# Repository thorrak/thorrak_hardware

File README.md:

# Thorrak's Hardware Designs
This repo is a collection of PCBs and other hardware designs I've made for various projects I've released. More information can be found on pages for each of the projects themselves.

**Note** - While the majority of the hardware for my projects is contained in this repo, the software is broken out into individual projects on GitHub. Most firmware can be flashed using [BrewFlasher](http://www.brewflasher.com/).

## BrewPi-ESP

The BrewPi-ESP project reimplements the BrewPi firmware on an ESP8266, ESP32, and ESP32-S2. 

- [Hardware Designs](BrewPi-ESP.md)
- [Project on GitHub](https://github.com/thorrak/brewpi-esp8266)

## TiltBridge

The TiltBridge project provides a Bluetooth-to-WiFi bridge for Tilt Hydrometers

- [Hardware/Container Designs](TiltBridge.md)
- [Project on GitHub](https://github.com/thorrak/tiltbridge/)

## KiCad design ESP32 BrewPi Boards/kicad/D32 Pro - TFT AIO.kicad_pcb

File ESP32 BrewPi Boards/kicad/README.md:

ESP32 BrewPi Controller Boards
==============================

# NOTE - This document is NOT complete/verified yet. 
## Please do not base a build on this doc without consulting Thorrak directly first!

Although the "heart" of a BrewPi controller is the microprocessor running the BrewPi-compatible firmware, without other connected components that microcontroller cannot sense temperature, control power, or do any of the other things that make a temperature controller useful. For the ESP32 version of this project, I have designed a single, "all-in-one" PCB that should work for virtually all builds. 

| Board Design                                              | Tindie Order Link                               | OSHPark Order Link                                     |
|-----------------------------------------------------------|-------------------------------------------------|--------------------------------------------------------|
| [All-in-One D32 / D32 Pro](D32%20Pro%20-%20-TFT%20AIO.md) | [Order](https://www.tindie.com/products/27251/) | [Order](https://oshpark.com/)  |

This board supports the following features:
- Supports both [LoLin D32](https://www.wemos.cc/en/latest/d32/d32.html) and [LoLin D32 Pro](https://www.wemos.cc/en/latest/d32/d32_pro.html) controllers
- Supports both IIC and TFT screens
- Supports both the specific [LoLin D32 Pro screen](https://www.aliexpress.com/item/2251832733414978.html), as well as generic TFT screens
- Supports emulating a NTC10k temperature sensor, allowing control of certain glycol chillers (IceMaster Max2/Max4 and possibly others)
- Selectable OneWire voltage
- Optional TH-only configuration for easy assembly

### About Parts Links, Order Links, & Vendors

The BOM links provided are intended to serve as examples of the parts needed and are not the only place to source the  parts listed.  Generally speaking, AliExpress is less expensive for parts.  The trade-off is that sometimes you are  buying 100 at a time, and in most cases you are waiting for shipping.  DigiKey, Mouser, or other project part suppliers  will probably have these parts as well and can generally ship much faster (albeit at much higher cost).

For convenience, order links are provided on each of the PCB's pages. Bare PCBs can be ordered from OshPark using the link provided, or from your PCB-vendor-of-choice by uploading the Gerber files (found in the `production` folder). I also sometimes have PCBs available for sale on Tindie - including in some cases, either fully- or partially-assembled boards. When you purchase through Tindie you are receiving a board or parts directly from me. 

#### TH Parts required to assemble the PCB

| Part                                                                                                                                       | Qty |
|--------------------------------------------------------------------------------------------------------------------------------------------|-----|
| [PCB](https://www.tindie.com/products/27251/)                                                                                              | 1   |
| [RJ45 Modular Jack w/no shield](https://www.digikey.com/en/products/detail/stewart-connector/SS-90000-001/14548964)                        | 1   |
| [2-terminal Screw Clamp](https://www.digikey.com/en/products/detail/w%C3%BCrth-elektronik/691137710002/6644051)                            | 1   |
| [4-Pin Male Pin Header](https://www.digikey.com/en/products/detail/sullins-connector-solutions/PRPC040SAAN-RC/2775214)                     | 2   |
| [3-Pin Male Pin Header](https://www.digikey.com/en/products/detail/sullins-connector-solutions/PRPC040SAAN-RC/2775214)                     | 1   |
| [2-Pin Male Pin Header](https://www.digikey.com/en/products/detail/sullins-connector-solutions/PRPC040SAAN-RC/2775214)                     | 1   |
| [16-Pin Female Pin Header](https://www.digikey.com/en/products/detail/sullins-connector-solutions/PPTC161LFBN-RC/810154)                   | 2   |
| [10-Pin (2x5) Box Header](https://www.digikey.com/en/products/detail/amphenol-cs-commercial-products/G821EU210AGM00Y/13683147) (Optional*) | 1   |
| [2.54mm Jumper](https://www.digikey.com/en/products/detail/sullins-connector-solutions/STC02SYAN/76372)**                                  | 1   |

*- The 10-pin box header is optional, but enables the use of a non-Lolin TFT screen attached to an LCD breakout PCB. If using an IIC screen or the [LoLin D32 Pro screen](https://www.aliexpress.com/item/2251832733414978.html) + [cable](https://www.aliexpress.com/item/2251832662518722.html), this can be left off.
**- The 2.54mm jumper is probably included on the 2-channel relay board you will purchase as part of the "common component" set below

### SMD Components required to assemble the PCB

Note - You will not need the following if you purchased the partially-assembled PCB from my [Tindie store](https://www.tindie.com/products/27251/). 

This board supports assembly with both SMD and TH components -- you can choose between the SMD components linked below and the TH components in the second table. You will not need both. The SMD components will enable the LCD2004 screen option - this screen will not work if you use the TH component set. 

| SMD Parts                                                                                                                     | Qty |
|-------------------------------------------------------------------------------------------------------------------------------|-----|
| [10k 0805 Resistor](https://www.digikey.com/en/products/detail/stackpole-electronics-inc/RNCP0805FTD10K0/2240262)             | 4   |
| [4.7k 0805 Resistor](https://www.digikey.com/en/products/detail/te-connectivity-passive-product/CRGCQ0805J4K7/8576740)        | 1   |
| [0.1uF (100nF) 0805 Capacitor](https://www.digikey.com/en/products/detail/samsung-electro-mechanics/CL21B104KACNNNC/3886757)  | 2   |
| [1.0uF 0805 Capacitor](https://www.digikey.com/en/products/detail/samsung-electro-mechanics/CL21B105KAFNNNE/3886724)          | 2   |
| [BSS138 MOSFET](https://www.digikey.com/en/products/detail/onsemi/BSS138/244210)                                              | 2   |
| [EL817S1(TU)-G Optocoupler](https://www.digikey.com/en/products/detail/everlight-electronics-co-ltd/EL8171S1-TU-G/9446028)    | 1   |
| [100R 0805 Resistor](https://www.digikey.com/en/products/detail/yageo/RC0805FR-07100RL/727543)                                | 1   |
| [8.2k 0805 Resistor](https://www.digikey.com/en/products/detail/stackpole-electronics-inc/RMCF0805JT8K20/1757870)             | 1   |
| [27k 0805 Resistor](https://www.digikey.com/en/products/detail/stackpole-electronics-inc/RMCF0805JT27K0/1757886)              | 1   |

This is the optional, alternative TH part set. You **DO NOT** need these parts if you ordered either the SMD parts above, or the partially-assembled PCB:

| Alternative TH Part                                                                                      | Qty |
|----------------------------------------------------------------------------------------------------------|-----|
| [4.7k Resistor](https://www.digikey.com/en/products/detail/stackpole-electronics-inc/CF14JT4K70/1741428) | 1   |
| [0.1uF (100nF) Capacitor](https://www.digikey.com/en/products/detail/kemet/C315C104M5U5TA/817927)        | 2   |
| [1.0uF Capacitor](https://www.digikey.com/en/products/detail/kemet/C320C105K5N5TA7301/12701373)          | 2   |

## Other Required Components

Below are the other "required" components for almost every build: 

| Component                                                                            | Qty |
|--------------------------------------------------------------------------------------|-----|
| [LOLIN D32 Pro](https://www.aliexpress.com/item/2251832696801305.html)               | 1   |
| [2-Channel 5V Relay Board](https://www.aliexpress.com/item/32997387727.html)         | 1   |
| [Ethernet cable](https://www.aliexpress.com/item/32694241950.html)                   | 1   |
| [5V 2A Power Supply Module](https://www.aliexpress.com/item/32900418425.html)        | 1   |
| [Dupont Cables (Female-to-Female)](https://www.aliexpress.com/item/33039596089.html) | 13* |

In addition to the above, this PCB is intended to be used in conjunction with a separate "Sensor Breakout Board" which is then connected to this PCB via the RJ-45 (ethernet) cable listed above. To complete a full controller, you will need the components listed on the [Sensor Board](../../BrewPi%20Sensor%20Boards/README.md) pages as well.

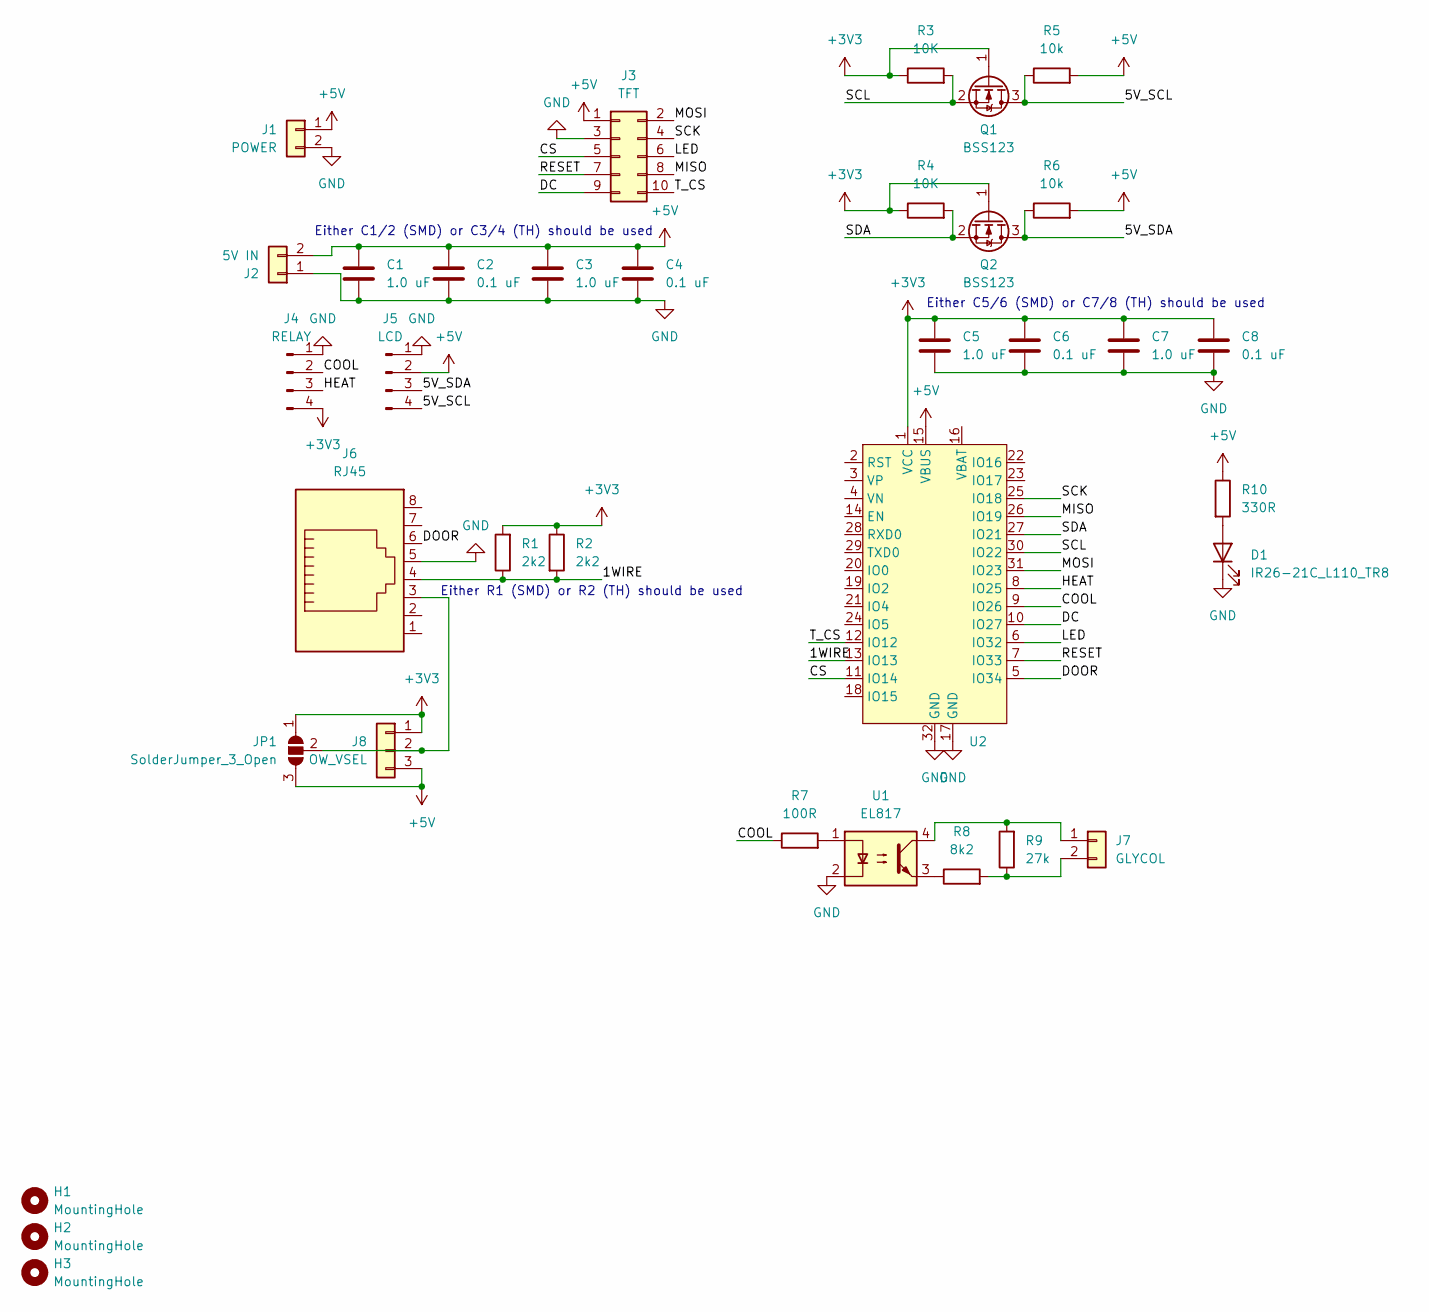
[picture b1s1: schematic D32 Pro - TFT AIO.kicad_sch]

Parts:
C1, C5: 1.0 uF; C_0805_2012Metric_Pad1.18x1.45mm_HandSolder; LCSC C28323
C2, C6: 0.1 uF; C_0805_2012Metric_Pad1.18x1.45mm_HandSolder; LCSC C49678
C3, C7: 1.0 uF; C_Disc_D3.0mm_W1.6mm_P2.50mm
C4, C8: 0.1 uF; C_Disc_D3.0mm_W1.6mm_P2.50mm
D1: IR26-21C_L110_TR8; LED_0805_2012Metric_Pad1.15x1.40mm_HandSolder; LCSC C2297
H1, H2, H3: MountingHole; MountingHole_3.2mm_M3
J1: POWER; PhoenixContact_MSTBVA_2,5_2-G-5,08_1x02_P5.08mm_Vertical
J2: 5V IN; PinHeader_1x02_P2.54mm_Vertical
J3: TFT; IDC-Header_2x05_P2.54mm_Vertical; LCSC C5665
J4: RELAY; PinHeader_1x04_P2.54mm_Vertical
J5: LCD; PinHeader_1x04_P2.54mm_Vertical
J6: RJ45; RJ45_Amphenol_54602-x08_Horizontal; LCSC C3000202
J7: GLYCOL; PinHeader_1x02_P2.54mm_Vertical
J8: OW_VSEL; PinHeader_1x03_P2.54mm_Vertical
JP1: SolderJumper_3_Open; SolderJumper-3_P1.3mm_Open_RoundedPad1.0x1.5mm
Q1, Q2: BSS123; SOT-23-3; LCSC C7420338
R1: 2k2; R_0805_2012Metric_Pad1.15x1.40mm_HandSolder; LCSC C17520
R2: 2k2; R_Axial_DIN0204_L3.6mm_D1.6mm_P1.90mm_Vertical
R3, R4: 10K; R_0805_2012Metric_Pad1.15x1.40mm_HandSolder; LCSC C17414
R5, R6: 10k; R_0805_2012Metric_Pad1.15x1.40mm_HandSolder; LCSC C17414
R7: 100R; R_0805_2012Metric_Pad1.15x1.40mm_HandSolder; LCSC C17408
R8: 8k2; R_0805_2012Metric_Pad1.15x1.40mm_HandSolder; LCSC C17828
R9: 27k; R_0805_2012Metric_Pad1.15x1.40mm_HandSolder; LCSC C17593
R10: 330R; R_0805_2012Metric_Pad1.20x1.40mm_HandSolder; LCSC C17630
U1: EL817; DIP-4_W8.89mm_SMDSocket_LongPads; LCSC C106900
U2: Lolin_D32

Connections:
+3V3: C5.1, C6.1, C7.1, C8.1, J4.4, J8.1, JP1.1 (A), Q1.1 (G), Q2.1 (G), R1.2, R2.1, R3.1, R4.1, U2.1 (VCC)
+5V: C1.1, C2.1, C3.1, C4.1, J1.1, J2.2, J3.1, J5.2, J8.3, JP1.3 (B), R5.2, R6.2, R10.1, U2.15 (VBUS)
/1WIRE: J6.4, R1.1, R2.2, U2.13 (IO13)
/5V_SCL: J5.4, Q1.3 (D), R5.1
/5V_SDA: J5.3, Q2.3 (D), R6.1
/COOL: J4.2, R7.1, U2.9 (IO26)
/CS: J3.5, U2.11 (IO14)
/DC: J3.9, U2.10 (IO27)
/DOOR: J6.6, U2.5 (IO34)
/HEAT: J4.3, U2.8 (IO25)
/LED: J3.6, U2.6 (IO32)
/MISO: J3.8, U2.26 (IO19)
/MOSI: J3.2, U2.31 (IO23)
/RESET: J3.7, U2.7 (IO33)
/SCK: J3.4, U2.25 (IO18)
/SCL: Q1.2 (S), R3.2, U2.30 (IO22)
/SDA: Q2.2 (S), R4.2, U2.27 (IO21)
/T_CS: J3.10, U2.12 (IO12)
GND: C1.2, C2.2, C3.2, C4.2, C5.2, C6.2, C7.2, C8.2, D1.1 (K), J1.2, J2.1, J3.3, J4.1, J5.1, J6.5, U1.2, U2.17 (GND), U2.32 (GND)
unnamed: D1.2 (A), R10.2
unnamed: J7.1, R9.2, U1.4
unnamed: J7.2, R8.2, R9.1
unnamed: J6.3, J8.2, JP1.2 (C)
unnamed: R7.2, U1.1
unnamed: R8.1, U1.3

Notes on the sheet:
Either C1/2 (SMD) or C3/4 (TH) should be used
Either R1 (SMD) or R2 (TH) should be used
Either C5/6 (SMD) or C7/8 (TH) should be used

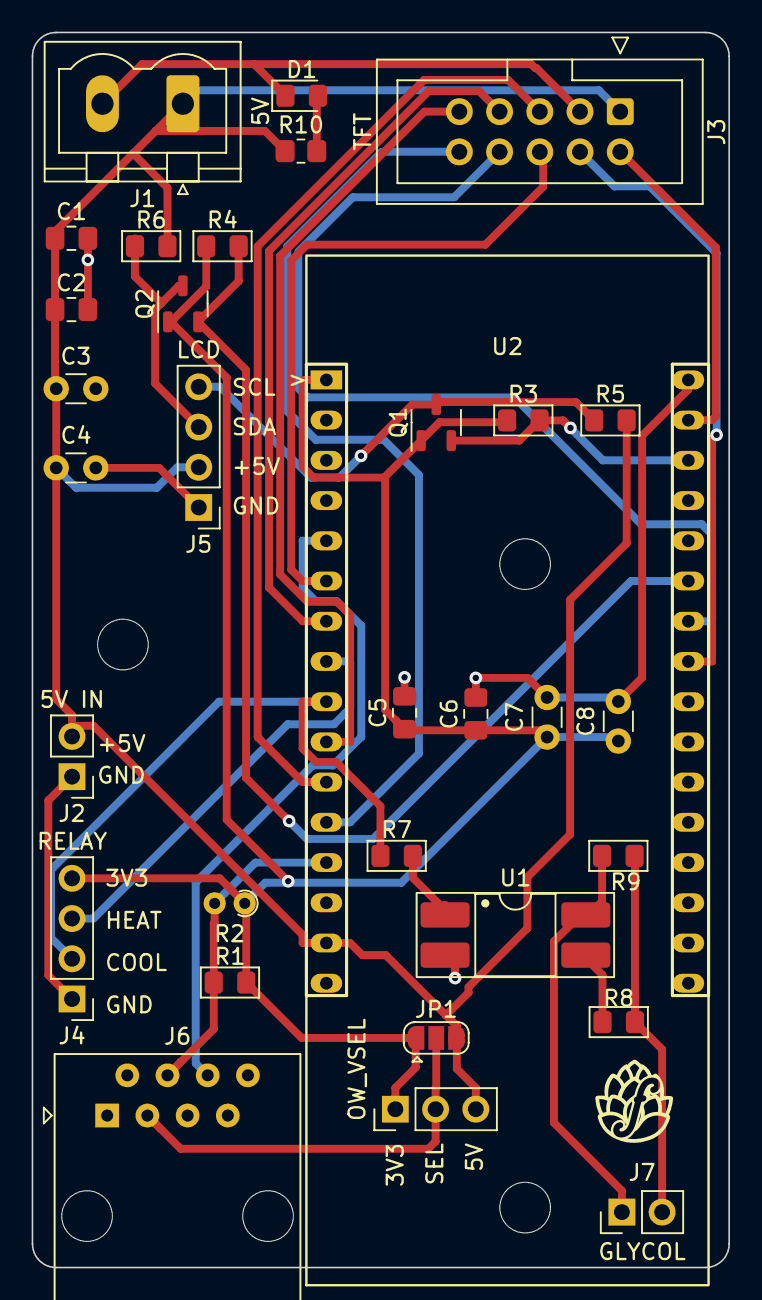
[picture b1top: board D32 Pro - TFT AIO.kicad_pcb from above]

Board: 2 copper layers, 44.0 x 78.0 mm, 35 parts (0 on the bottom side), 25 nets.

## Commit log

2019-12-01 Adding boards
2019-12-01 Fix relative links
2019-12-06 Updating to latest
2020-05-31 Add voltage selection to SMD boards
2020-05-31 Add SMD notes & remove links to pcbs.io
2020-05-31 remove ds store
2020-05-31 Bring up to date
2020-05-31 Removing ds_store
2020-05-31 Updating LCD TH Dupont design
2020-05-31 Updating readme
2020-05-31 Updating images
2020-05-31 Updating No LCD Boards
2020-05-31 Update No LCD board
2020-05-31 Updating TH Screw board
2020-05-31 Add common components language
2020-05-31 Update RJ-45 Board Design
2020-06-02 Update sensor breakout boards
2020-06-02 Add project pages
2020-06-02 Add the majority of the main container files
2020-06-02 Finalize main PCB BOM
2020-06-02 Update case lid info
2020-06-03 Adding sensor box info
2020-06-03 Updating board designs and adding DirtyPCB Links
2020-06-05 Update sensor breakout board
2020-06-05 Updating text/links
2020-06-06 Update sensor breakout container
2020-06-06 Update tindie links
2020-06-06 Add Boards
2020-10-06 Add NoRJ PCB
2020-10-06 Fix PCB link
2021-01-01 Adding BrewPi Containers
2021-01-01 Add TiltBridge containers
2021-02-01 Updated TiltBridge containers
2021-02-15 Add TTGO USBC case for TiltBridge
2021-02-15 Update readmes
2021-03-12 Add solder bridge to SMD board design
2022-02-28 Add prusaprinters links
2022-05-07 Update file modes
2022-05-09 Update BoMs and add DigiKey links
2022-06-29 Add controller selection grid
2022-07-11 Add D32 PCBs
2022-07-11 Update ESP32 readme
2023-11-01 Redraw PCB in KiCad 7.0
    Redraw schematic and PCB layout using KiCad 7.0. Add circuit to emulate NTC10k temp sensor.
2023-11-02 Fix footprint for U1
2023-11-10 Add schematic note
2023-12-04 Power to OneWire sensors
    Add trace for power to onewire sensors, adjust silkscreen
2024-12-13 Update project name The BrewPi-ESP8266 project is now known as BrewPi-ESP given the move to reduce support for the ESP8266
2024-12-13 Add RJ-11 and RJ-45 jack breakouts
2024-12-13 Add LoLin D32 v1.1.0 case lid design
2024-12-13 Rename AIO PCB to "OneSize" Renaming the existing AIO PCB as there is a new, true, all-in-one design coming
2024-12-19 Update RJ-45 Sensor Breakout - Updates documentation for board - Adds LCSC part numbers & JLC offsets to design files - Adds JLC BOM/CPL to repo
2024-12-19 Clean up "other" boards
2024-12-20 Add new "BrewPi-ESP Test" Boards These boards take the place of a full BrewPi build for testing new firmware
2024-12-20 Add new "All-in-One" PCBs These PCBs integrate the 2-channel relay board and power supply into a single PCB
2024-12-20 Add case for new "All-in-One" PCBs
2024-12-20 Fix links
2025-03-27 Update Sensor Box designs
2025-03-27 Add updated AIO case design
2025-03-31 Update US Outlet.md
    Adds Tindie link, updates description to describe the PCB better.
2025-03-31 Update AIO US Outlet.md
    Add Tindie link and provisional Bill of Materials
2025-03-31 Update D32 Pro - TFT OneSize.md
    Updates Tindie links and explains discrete components
2025-03-31 Update Single PCB - IRM-10-5.md
    Update Tindie links, pricing, and add note about the case design
2025-03-31 Update Single PCB - PSK-10D-5.md
    Update Tindie link, add note about power supply
2025-04-03 Reorganize Main PCB Container Files
2025-04-03 Add updated main PCB case designs
2025-04-08 Add 3.2in AIO case lid
2025-04-08 Add YouTube Video
2025-04-12 Reorganize
2025-04-16 Add LoLin Bracket STL
